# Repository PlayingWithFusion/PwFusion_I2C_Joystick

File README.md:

# PwFusion_I2C_Joystick

Are you looking for a way to take your project to the next level? Playing with Fusion's I2C Joystick board is the way to go! This device greatly simplifies connectivity to a microcontroller through the QWIIC system. The typical 5 wires required to use a joystick componet with a microcontroller can be reduced to one QWIIC cable. You can even chain multiple QWIIC devices together for maximum wiring efficiency! If that isn't enough, Playing with Fusion provides Arduino libraries to make writing code for these boards as easy as possible! Weather you are a beginner looking for a simple introduction to the world of hobbyist electronics or an advanced user looking for a rapid prototyping tool, Playing with Fusion's I2C Joystick is right for you!

## I2C Addresses

| ADR 0   |   ADR 1   |   Address |
| --- | --- | --- |
| uncut   |   uncut   |   0x05 |
| cut     |   uncut   |   0x06 |
| uncut   |   cut     |   0x07 |
| cut     |   cut     |   0x08 |

The Playing with Fusion I2C joystick board comes with 4 available I2C addresses, which can be easily selected by cutting the jumpers on the printed circuit board. This allows for 4 joystick boards to be used on the same QWIIC chain. If you would like more than 4, see docs/Programming Instructions and flash a modified firmware with additional I2C address options.

## Example Projects
RC Transmitter: https://github.com/PlayingWithFusion/RC_Transmitter

## Related
| Page | Link |
| --- | --- |
| PwFusion_I2C_Joystick_Arduino_Library: | https://github.com/PlayingWithFusion/PwFusion_I2C_Joystick_Arduino_Library |
| PwFusion_Data_Transfer:                | https://github.com/PlayingWithFusion/PwFusion_Data_Transfer |
| IFB-40001 PwFusion_I2C_Encoder:  |   https://github.com/PlayingWithFusion/PwFusion_I2C_Encoder |
| IFB-40002 PwFusion_I2C_Joystick: |   https://github.com/PlayingWithFusion/PwFusion_I2C_Joystick |
| IFB-40003 PwFusion_I2C_Switch:   |   https://github.com/PlayingWithFusion/PwFusion_I2C_Switch |
| IFB-40004 PwFusion_I2C_Buttons:  |   https://github.com/PlayingWithFusion/PwFusion_I2C_Buttons |

Visit https://www.playingwithfusion.com/ for more information.

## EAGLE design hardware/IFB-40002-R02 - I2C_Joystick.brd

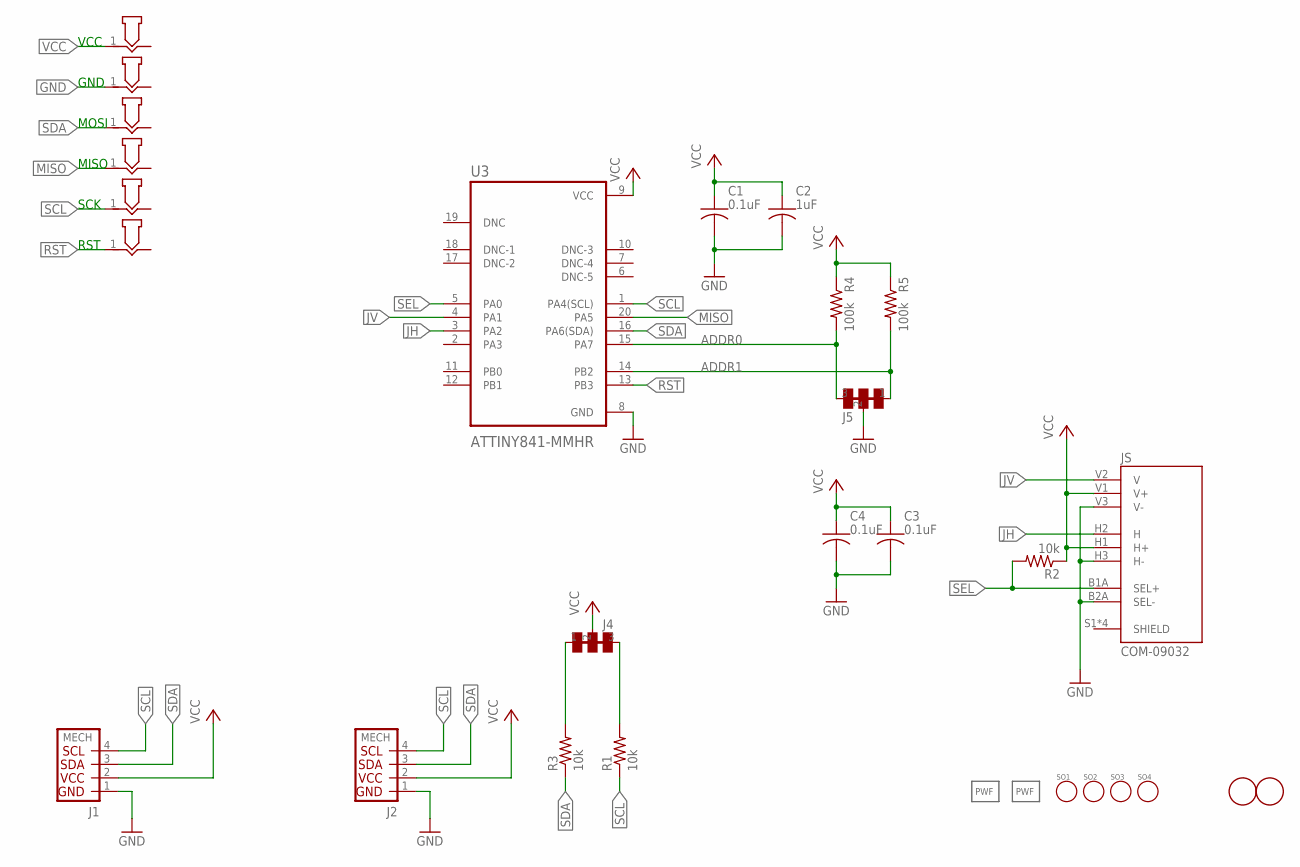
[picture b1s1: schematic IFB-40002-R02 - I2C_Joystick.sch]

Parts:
C1, C3, C4: 0.1uF; C0603K
C2: 1uF; C0603K
GND: POGO_PAD; P50_POGO_BOARD_CONTACT_12MIL
J1, J2: QWIICSIDE; SM04B-SRSS-TB
J4, J5: CUT_JUMPER_2X; SMT_2X_CUTTABLE_JUMPER
JS: COM-09032; XDCR_COM-09032
LOGO1, LOGO2: PWF_LOGOPWF-6MM-SS; LOGO_6MM_STEIN
MISO: POGO_PAD; P50_POGO_BOARD_CONTACT_12MIL
MOSI: POGO_PAD; P50_POGO_BOARD_CONTACT_12MIL
R1, R2, R3: 10k; R0603
R4, R5: 100k; R0603
RST: POGO_PAD; P50_POGO_BOARD_CONTACT_12MIL
SCK: POGO_PAD; P50_POGO_BOARD_CONTACT_12MIL
SO1, SO2, SO3, SO4: STAND_OFFNO4_TIGHT; STANDOFF_NO4_TIGHT
U3: ATTINY841-MMHR; QFN45P300X300X85-21N
U$2, U$3: FIDUCIAL; FIDUCIAL_1MM
VCC: POGO_PAD; P50_POGO_BOARD_CONTACT_12MIL

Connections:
ADDR0: J5.3, R4.2, U3.15 (PA7)
ADDR1: J5.1, R5.2, U3.14 (PB2)
GND: C1.2, C2.2, C3.2, C4.2, GND.1, J1.1, J2.1, J5.2, JS.B2A (SEL-), JS.H3 (H-), JS.V3 (V-), U3.8 (GND)
JH: JS.H2 (H), U3.3 (PA2)
JV: JS.V2 (V), U3.4 (PA1)
MISO: MISO.1, U3.20 (PA5)
unnamed: J4.1, R3.2
unnamed: J4.3, R1.2
RST: RST.1, U3.13 (PB3)
SCL: J1.4, J2.4, R1.1, SCK.1, U3.1 (PA4(SCL))
SDA: J1.3, J2.3, MOSI.1, R3.1, U3.16 (PA6(SDA))
SEL: JS.B1A (SEL+), R2.2, U3.5 (PA0)
VCC: C1.1, C2.1, C3.1, C4.1, J1.2, J2.2, J4.2, JS.H1 (H+), JS.V1 (V+), R2.1, R4.1, R5.1, U3.9 (VCC), VCC.1

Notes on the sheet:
VCC
GND
MOSI
MISO
SCK
RST

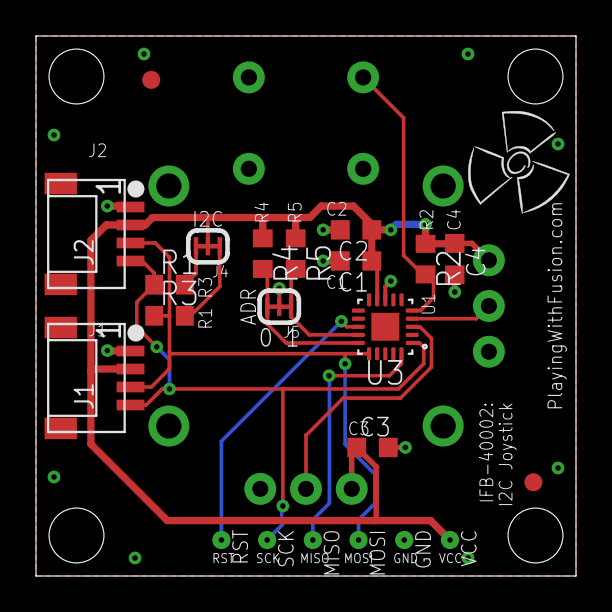
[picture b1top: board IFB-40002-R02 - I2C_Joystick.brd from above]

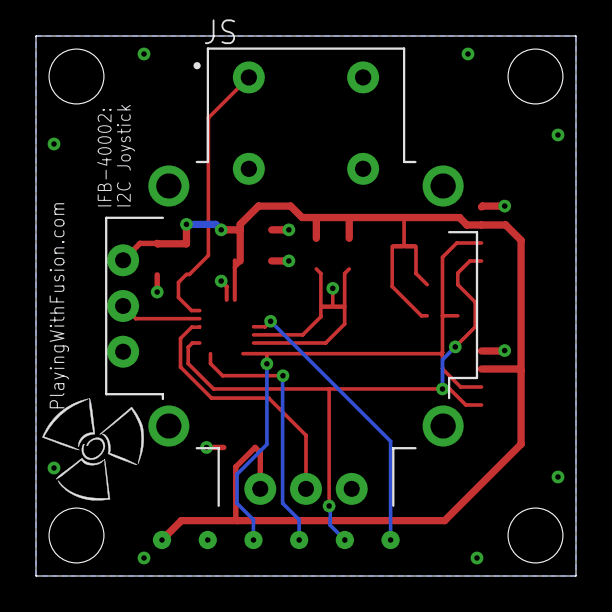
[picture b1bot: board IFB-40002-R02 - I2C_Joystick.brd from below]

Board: 2 copper layers, 30.0 x 30.0 mm, 29 parts (2 on the bottom side), 13 nets.

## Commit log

2023-10-01 Added firmware and readme
2023-10-08 hardware and links
2023-10-29 added programming instructions
2023-12-02 updated addresses
2023-12-02 updated hardware files
2024-07-05 updated firmware flash instructions
